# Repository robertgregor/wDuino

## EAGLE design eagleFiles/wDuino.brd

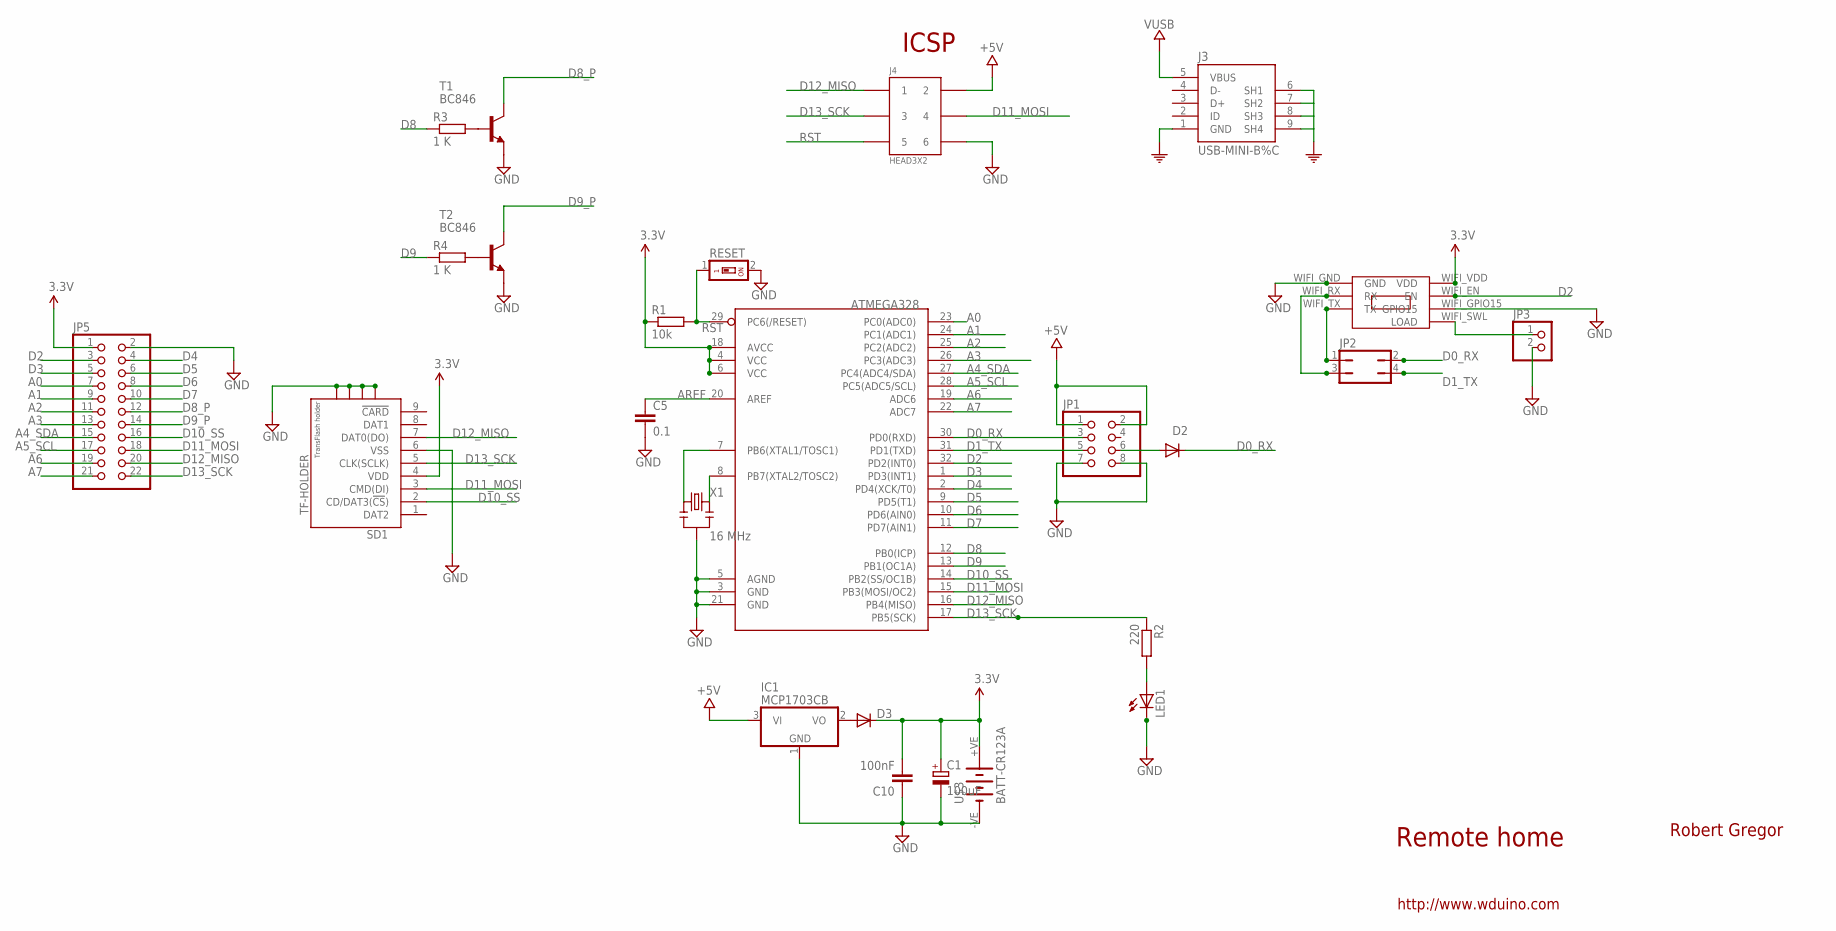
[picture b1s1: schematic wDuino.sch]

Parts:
ATMEGA328: ATMega-328; TQFP32-08
C1: 100uF; SMC_B
C5: 0.1; C0603
C10: 100nF; C0603
D2: DIODE-SOD123; SOD123
D3: DIODE-DO214AC; DO214AC
IC1: MCP1703CB; SOT23
J3: USB-MINI-B%C; USB-MINI-B_2
J4: HEAD3X2
JP1: PINHD-2X4; 2X04
JP2: JP2Q
JP3: PINHD-1X2; 1X02
JP5: PINHD-2X11; 2X11
LED1: LEDSML0603; SML0603
R1: 10k; R0603
R2: 220; R0603
R3, R4: 1 K; R0603
RESET: SWS001; SMS-001
SD1: TF-HOLDER; TF-PULL
T1, T2: BC846; SOT23
U$3: BATT-CR123A; KEYSTONE-2/3A
U$5: ESP03
X1: 16 MHz; RESONATOR-SMD

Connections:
5V: IC1.3 (VI), J3.5 (VBUS), J4.2, JP1.1, JP1.2
A0: ATMEGA328.23 (PC0(ADC0)), JP5.7
A1: ATMEGA328.24 (PC1(ADC1)), JP5.9
A2: ATMEGA328.25 (PC2(ADC2)), JP5.11
A3: ATMEGA328.26 (PC3(ADC3)), JP5.13
A4_SDA: ATMEGA328.27 (PC4(ADC4/SDA)), JP5.15
A5_SCL: ATMEGA328.28 (PC5(ADC5/SCL)), JP5.17
A6: ATMEGA328.19 (ADC6), JP5.19
A7: ATMEGA328.22 (ADC7), JP5.21
AREF: ATMEGA328.20 (AREF), C5.1
D0_RX: ATMEGA328.30 (PD0(RXD)), D2.C, JP1.3, JP2.2
D1_TX: ATMEGA328.31 (PD1(TXD)), JP1.5, JP2.4
D2: ATMEGA328.32 (PD2(INT0)), JP5.3, U$5.WIFI_EN (EN)
D3: ATMEGA328.1 (PD3(INT1)), JP5.5
D4: ATMEGA328.2 (PD4(XCK/T0)), JP5.4
D5: ATMEGA328.9 (PD5(T1)), JP5.6
D6: ATMEGA328.10 (PD6(AIN0)), JP5.8
D7: ATMEGA328.11 (PD7(AIN1)), JP5.10
D8: ATMEGA328.12 (PB0(ICP)), R3.1
D8_P: JP5.12, T1.3 (C)
D9: ATMEGA328.13 (PB1(OC1A)), R4.1
D9_P: JP5.14, T2.3 (C)
D10_SS: ATMEGA328.14 (PB2(SS/OC1B)), JP5.16, SD1.2 (CD/DAT3(!CS!))
D11_MOSI: ATMEGA328.15 (PB3(MOSI/OC2)), J4.4, JP5.18, SD1.3 (CMD(DI))
D12_MISO: ATMEGA328.16 (PB4(MISO)), J4.1, JP5.20, SD1.7 (DAT0(DO))
D13_SCK: ATMEGA328.17 (PB5(SCK)), J4.3, JP5.22, R2.1, SD1.5 (CLK(SCLK))
GND: ATMEGA328.3 (GND), ATMEGA328.5 (AGND), ATMEGA328.21 (GND), C1.-, C5.2, C10.1, IC1.1 (GND), J3.1 (GND), J3.6 (SH1), J3.7 (SH2), J3.8 (SH3), J3.9 (SH4), J4.6, JP1.7, JP1.8, JP3.2, JP5.2, LED1.C, RESET.2, SD1.6 (VSS), SD1.S1, SD1.S2, SD1.S3, SD1.S4, T1.2 (E), T2.2 (E), U$3.-VE (-), U$5.WIFI_GND (GND), U$5.WIFI_GPIO15 (GPIO15), X1.2
unnamed: ATMEGA328.7 (PB6(XTAL1/TOSC1)), X1.1
unnamed: D3.A, IC1.2 (VO)
unnamed: LED1.A, R2.2
unnamed: JP3.1, U$5.WIFI_SWL (LOAD)
unnamed: R4.2, T2.1 (B)
unnamed: D2.A, JP1.6
unnamed: R3.2, T1.1 (B)
unnamed: JP2.1, U$5.WIFI_TX (TX)
unnamed: JP2.3, U$5.WIFI_RX (RX)
unnamed: ATMEGA328.8 (PB7(XTAL2/TOSC2)), X1.3
RST: ATMEGA328.29 (PC6(/RESET)), J4.5, R1.2, RESET.1
VCC: ATMEGA328.4 (VCC), ATMEGA328.6 (VCC), ATMEGA328.18 (AVCC), C1.+, C10.2, D3.C, JP5.1, R1.1, SD1.4 (VDD), U$3.+VE (+), U$5.WIFI_VDD (VDD)

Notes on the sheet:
Remote home
Robert Gregor
http://www.wduino.com
ICSP

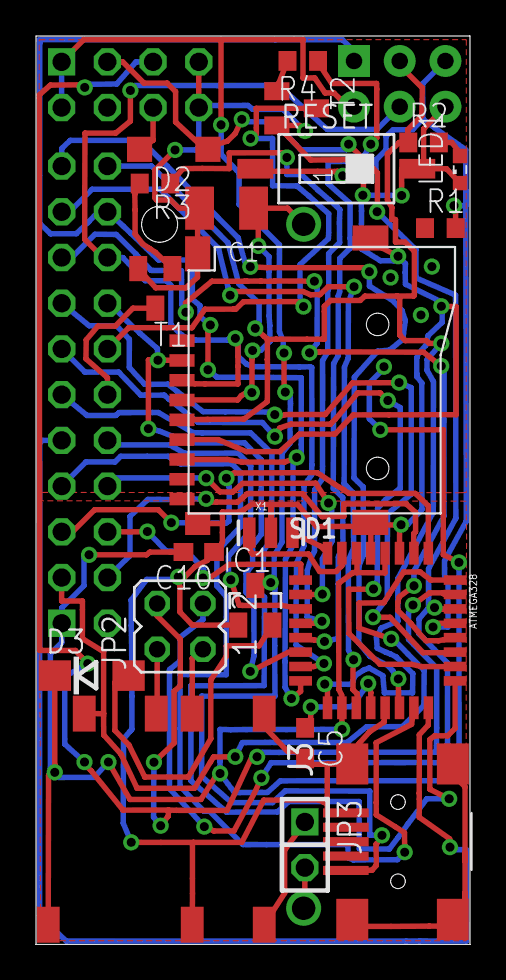
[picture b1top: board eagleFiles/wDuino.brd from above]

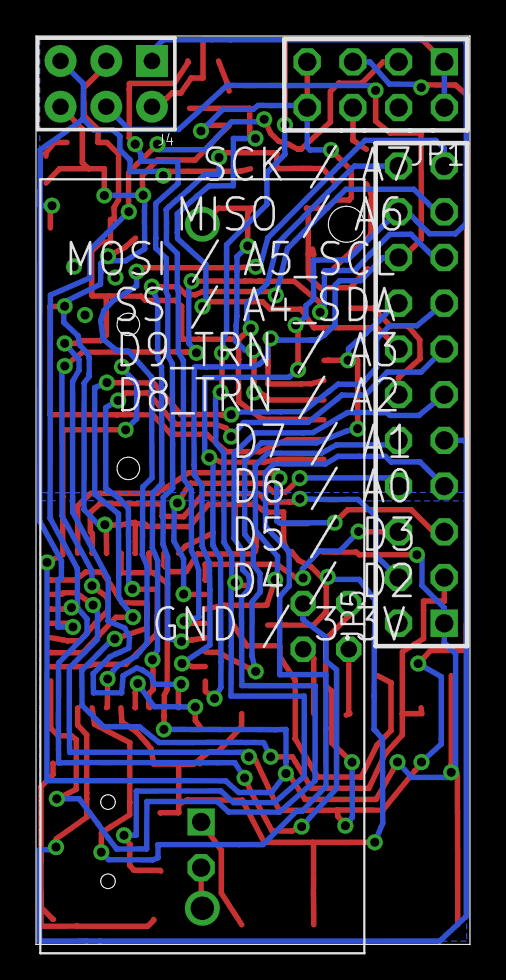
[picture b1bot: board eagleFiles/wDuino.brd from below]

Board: 2 copper layers, 24.1 x 50.5 mm, 25 parts (4 on the bottom side), 39 nets.

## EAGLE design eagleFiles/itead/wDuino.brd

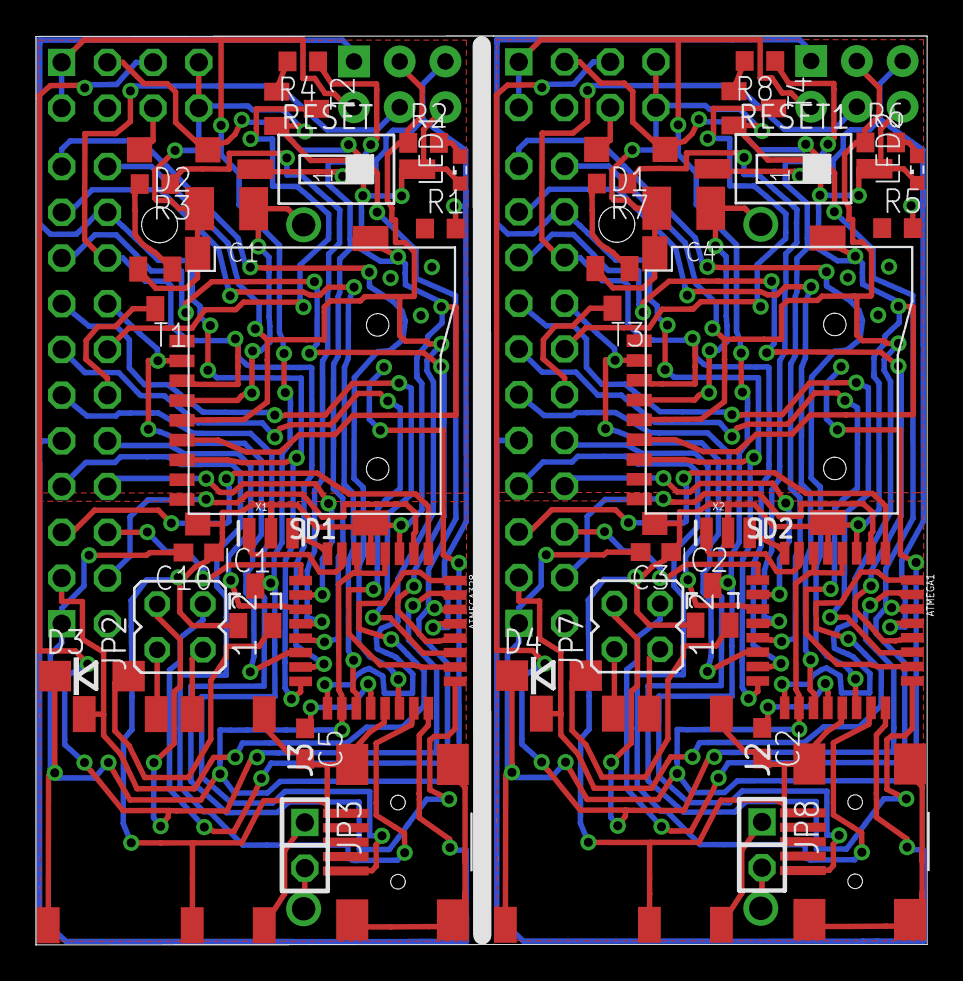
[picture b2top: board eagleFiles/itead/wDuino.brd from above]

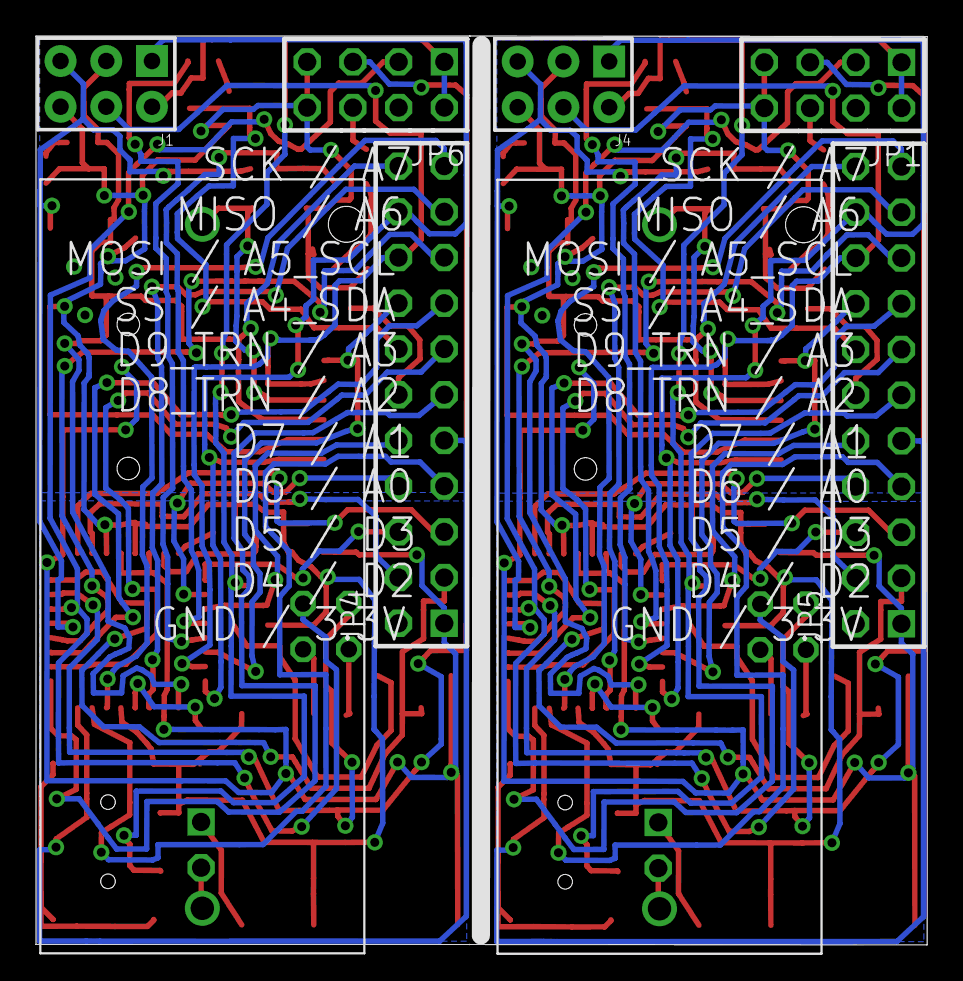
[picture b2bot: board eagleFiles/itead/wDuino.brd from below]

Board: 2 copper layers, 49.5 x 50.5 mm, 50 parts (8 on the bottom side), 78 nets.

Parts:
ATMEGA1, ATMEGA328: ATMega-328; TQFP32-08
C1, C4: 100uF; SMC_B
C2, C5: 0.1; C0603
C3, C10: 100nF; C0603
D1, D2: SOD123
D3, D4: DO214AC
IC1, IC2: MCP1703CB; SOT23
J1, J4: HEAD3X2
J2, J3: USB-MINI-B%C; USB-MINI-B_2
JP1, JP6: 2X04
JP2, JP7: JP2Q
JP3, JP8: 1X02
JP4, JP5: 2X11
LED1, LED2: SML0603
R1, R5: 10k; R0603
R2, R6: 220; R0603
R3, R4, R7, R8: 1 K; R0603
RESET, RESET1: SMS-001
SD1, SD2: TF-HOLDER; TF-PULL
T1, T2, T3, T4: BC846; SOT23
U$1, U$3: BATT-CR123A; KEYSTONE-2/3A
U$2, U$5: ESP03
X1, X2: 16 MHz; RESONATOR-SMD

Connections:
5V: IC1.3, J3.5, J4.2, JP1.1, JP1.2
5V1: IC2.3, J1.2, J2.5, JP6.1, JP6.2
A0: ATMEGA328.23, JP5.7
A1: ATMEGA328.24, JP5.9
A2: ATMEGA328.25, JP5.11
A3: ATMEGA328.26, JP5.13
A4: ATMEGA1.22, JP4.21
A4_SDA: ATMEGA328.27, JP5.15
A4_SDA1: ATMEGA1.27, JP4.15
A5: ATMEGA1.19, JP4.19
A5_SCL: ATMEGA328.28, JP5.17
A5_SCL1: ATMEGA1.28, JP4.17
A6: ATMEGA328.19, JP5.19
A7: ATMEGA328.22, JP5.21
A8: ATMEGA1.26, JP4.13
A9: ATMEGA1.25, JP4.11
A10: ATMEGA1.24, JP4.9
A11: ATMEGA1.23, JP4.7
AREF: ATMEGA328.20, C5.1
AREF1: ATMEGA1.20, C2.1
D0_RX: ATMEGA328.30, D2.C, JP1.3, JP2.2
D0_RX1: ATMEGA1.30, D1.C, JP6.3, JP7.2
D1: ATMEGA1.13, R8.1
D1_TX: ATMEGA328.31, JP1.5, JP2.4
D1_TX1: ATMEGA1.31, JP6.5, JP7.4
D2: ATMEGA328.32, JP5.3, U$5.WIFI_EN
D3: ATMEGA328.1, JP5.5
D4: ATMEGA328.2, JP5.4
D5: ATMEGA328.9, JP5.6
D6: ATMEGA328.10, JP5.8
D7: ATMEGA328.11, JP5.10
D8: ATMEGA328.12, R3.1
D8_P: JP5.12, T1.3
D8_P1: JP4.12, T3.3
D9: ATMEGA328.13, R4.1
D9_P: JP5.14, T2.3
D9_P1: JP4.14, T4.3
D10: ATMEGA1.12, R7.1
D10_SS: ATMEGA328.14, JP5.16, SD1.2
D10_SS1: ATMEGA1.14, JP4.16, SD2.2
D11: ATMEGA1.11, JP4.10
D11_MOSI: ATMEGA328.15, J4.4, JP5.18, SD1.3
D11_MOSI1: ATMEGA1.15, J1.4, JP4.18, SD2.3
D12: ATMEGA1.10, JP4.8
D12_MISO: ATMEGA328.16, J4.1, JP5.20, SD1.7
D12_MISO1: ATMEGA1.16, J1.1, JP4.20, SD2.7
D13: ATMEGA1.9, JP4.6
D13_SCK: ATMEGA328.17, J4.3, JP5.22, R2.1, SD1.5
D13_SCK1: ATMEGA1.17, J1.3, JP4.22, R6.1, SD2.5
D14: ATMEGA1.2, JP4.4
D15: ATMEGA1.1, JP4.5
D16: ATMEGA1.32, JP4.3, U$2.WIFI_EN
GND: ATMEGA328.3, ATMEGA328.5, ATMEGA328.21, C1.-, C5.2, C10.1, IC1.1, J3.1, J3.6, J3.7, J3.8, J3.9, J4.6, JP1.7, JP1.8, JP3.2, JP5.2, LED1.C, RESET.2, SD1.6, SD1.S1, SD1.S2, SD1.S3, SD1.S4, T1.2, T2.2, U$3.-VE, U$5.WIFI_GND, U$5.WIFI_GPIO15, X1.2
GND1: ATMEGA1.3, ATMEGA1.5, ATMEGA1.21, C2.2, C3.1, C4.-, IC2.1, J1.6, J2.1, J2.6, J2.7, J2.8, J2.9, JP4.2, JP6.7, JP6.8, JP8.2, LED2.C, RESET1.2, SD2.6, SD2.S1, SD2.S2, SD2.S3, SD2.S4, T3.2, T4.2, U$1.-VE, U$2.WIFI_GND, U$2.WIFI_GPIO15, X2.2
unnamed: ATMEGA328.7, X1.1
unnamed: D3.A, IC1.2
unnamed: ATMEGA1.7, X2.1
unnamed: LED1.A, R2.2
unnamed: JP3.1, U$5.WIFI_SWL
unnamed: R4.2, T2.1
unnamed: D2.A, JP1.6
unnamed: R3.2, T1.1
unnamed: ATMEGA1.8, X2.3
unnamed: JP2.1, U$5.WIFI_TX
unnamed: JP2.3, U$5.WIFI_RX
unnamed: JP7.1, U$2.WIFI_TX
unnamed: JP7.3, U$2.WIFI_RX
unnamed: LED2.A, R6.2
unnamed: D1.A, JP6.6
unnamed: R7.2, T3.1
unnamed: R8.2, T4.1
unnamed: D4.A, IC2.2
unnamed: JP8.1, U$2.WIFI_SWL
unnamed: ATMEGA328.8, X1.3
RST: ATMEGA328.29, J4.5, R1.2, RESET.1
RST1: ATMEGA1.29, J1.5, R5.2, RESET1.1
VCC: ATMEGA328.4, ATMEGA328.6, ATMEGA328.18, C1.+, C10.2, D3.C, JP5.1, R1.1, SD1.4, U$3.+VE, U$5.WIFI_VDD
VCC1: ATMEGA1.4, ATMEGA1.6, ATMEGA1.18, C3.2, C4.+, D4.C, JP4.1, R5.1, SD2.4, U$1.+VE, U$2.WIFI_VDD

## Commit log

2015-03-09 Initial version
    Initial version of the wDuino

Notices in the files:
parts and their libraries:
eagle-library-edeca.net-v5: This is v1 and is licensed under the Creative Commons (Attribution-Non-Commercial-Share Alike 2.0 UK)
